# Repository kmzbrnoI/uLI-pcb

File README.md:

uLI – Ultimate LI PCB
=====================

uLI is a XpressNET &#8596; USB converter behaving as COM port in PC (CDC).

## uLI v5

* Designed in: KiCad 7
* Main Processor: PIC18F14K50
* Several enhancements from uLI v4, backward-compatible.
  - See releases/tags for a list of modifications from uLI v4.
* Firmware is same for v4 & v5.
* Authors: Jan Horacek (c) 2024

## uLI v4

* Deprecated.
* Designed in: Eagle 9
* Main Processor: PIC18F14K50
* Authors: Jan Horacek, Michal Petrilak (c) 2016

## Firmware

* [uLI-fw](https://github.com/kmzbrnoI/uLI-fw)
* [uLI-master-fw](https://github.com/kmzbrnoI/uLI-master-fw)

## Further reading

- [About XpressNET](http://www.opendcc.de/info/xpressnet/xpressnet_e.html)
- uLI meets [XpressNET specification v3](http://www.lenzusa.com/1newsite1/Manuals/xpressnet.pdf)
- uLI should also meet [XpressNET specification v3.6](http://wiki.rocrail.net/lib/exe/fetch.php?id=xpressnet-en&cache=cache&media=xpressnet:xpressnet-lan-usb-23151-v1.pdf) (available only in German)

## License

Content of the repository is provided under [Creative Commons
Attribution-ShareAlike 4.0
License](https://creativecommons.org/licenses/by-sa/4.0/) as openhardware
project. You may download any data, contribute to the project, create PCB
yourself or even sell it yourself.

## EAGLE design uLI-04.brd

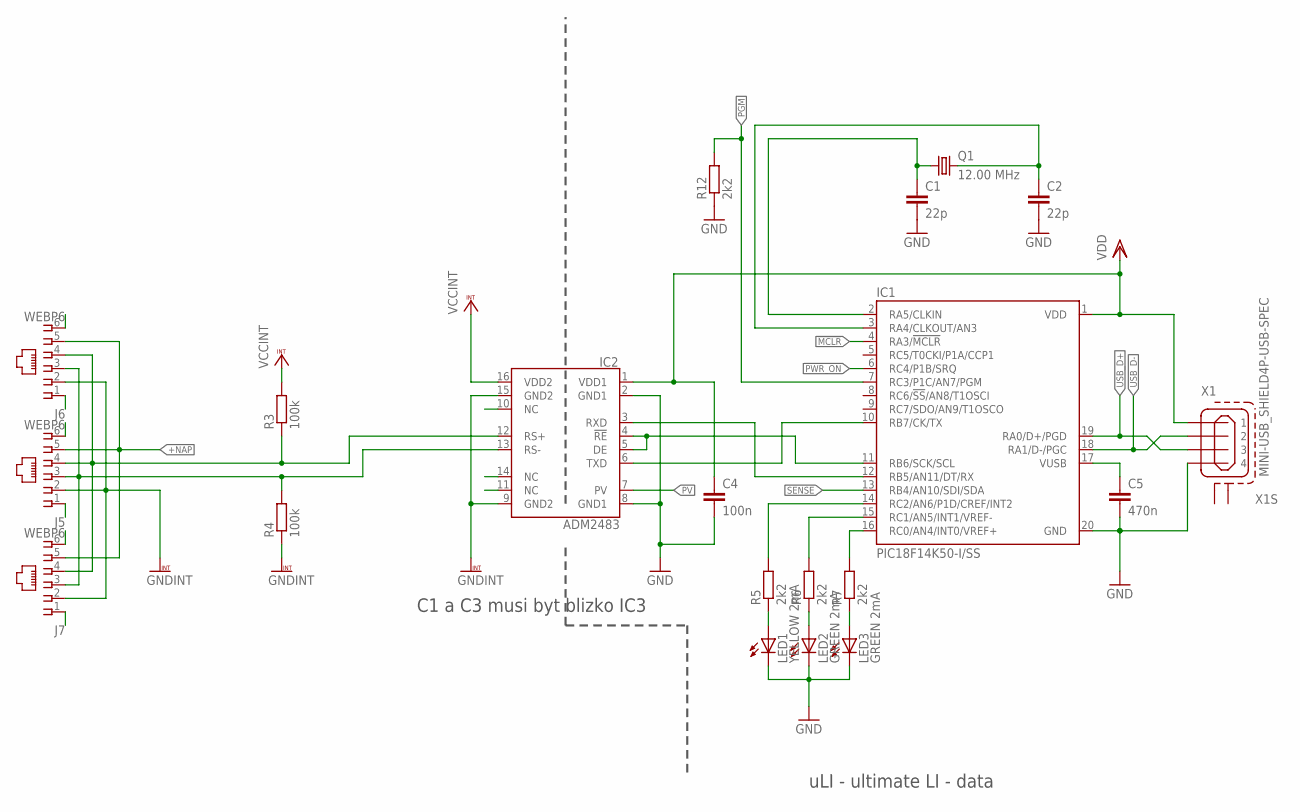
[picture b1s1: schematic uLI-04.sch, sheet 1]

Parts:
C1, C2: 22p; C0805
C4: 100n; C1206
C5: 470n; C1206
IC1: PIC18F14K50-I/SS; SSOP20
IC2: ADM2483; SO-16W
J5, J6, J7: WEBP6; WEBP6-6_SPEC2
LED1: YELLOW 2mA; LED3MM
LED2, LED3: GREEN 2mA; LED3MM
Q1: 12.00 MHz; HC49U70
R3, R4: 100k; R1206
R5, R6, R7, R12: 2k2; R1206
X1: MINI-USB_SHIELD4P-USB-SPEC; 85-32004-10X-SPEC

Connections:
!MCLR: IC1.4 (RA3/!MCLR!); also elsewhere on the board
+NAP: J5.5, J6.5, J7.5; also elsewhere on the board
BUS_A: IC2.12 (RS+), J5.4, J6.4, J7.4, R3.1
BUS_B: IC2.13 (RS-), J5.3, J6.3, J7.3, R4.2
GND: C1.2, C2.2, C4.2, C5.2, IC1.20 (GND), IC2.2 (GND1), IC2.8 (GND1), LED1.K (C), LED2.K (C), LED3.K (C), R12.1, X1.4; also elsewhere on the board
GNDINT: IC2.9 (GND2), IC2.15 (GND2), J5.2, J6.2, J7.2, R4.1; also elsewhere on the board
LED1: IC1.14 (RC2/AN6/P1D/CREF/INT2), R5.2
LED1_R: LED1.A, R5.1
LED2: IC1.15 (RC1/AN5/INT1/VREF-), R6.2
LED2_R: LED2.A, R6.1
LED3: IC1.16 (RC0/AN4/INT0/VREF+), R7.2
LED3_R: LED3.A, R7.1
unnamed: IC1.12 (RB5/AN11/DT/RX), IC2.3 (RXD)
NC2: IC2.14 (NC)
PGM: IC1.7 (RC3/P1C/AN7/PGM), R12.2; also elsewhere on the board
PROC_RX: IC1.10 (RB7/CK/TX), IC2.6 (TXD)
PROC_TE: IC1.11 (RB6/SCK/SCL), IC2.4 (!RE), IC2.5 (DE)
PV: IC2.7 (PV); also elsewhere on the board
PWR_ON: IC1.6 (RC4/P1B/SRQ); also elsewhere on the board
SENSE: IC1.13 (RB4/AN10/SDI/SDA); also elsewhere on the board
USB_D+: IC1.19 (RA0/D+/PGD), X1.3; also elsewhere on the board
USB_D-: IC1.18 (RA1/D-/PGC), X1.2; also elsewhere on the board
VBUS: C5.1, IC1.17 (VUSB)
VCCINT: IC2.16 (VDD2), R3.2; also elsewhere on the board
VDD: C4.1, IC1.1 (VDD), IC2.1 (VDD1), X1.1; also elsewhere on the board
XTAL1: C1.1, IC1.2 (RA5/CLKIN), Q1.1
XTAL2: C2.1, IC1.3 (RA4/CLKOUT/AN3), Q1.2

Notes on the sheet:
uLI - ultimate LI - data
C1 a C3 musi byt blizko IC3

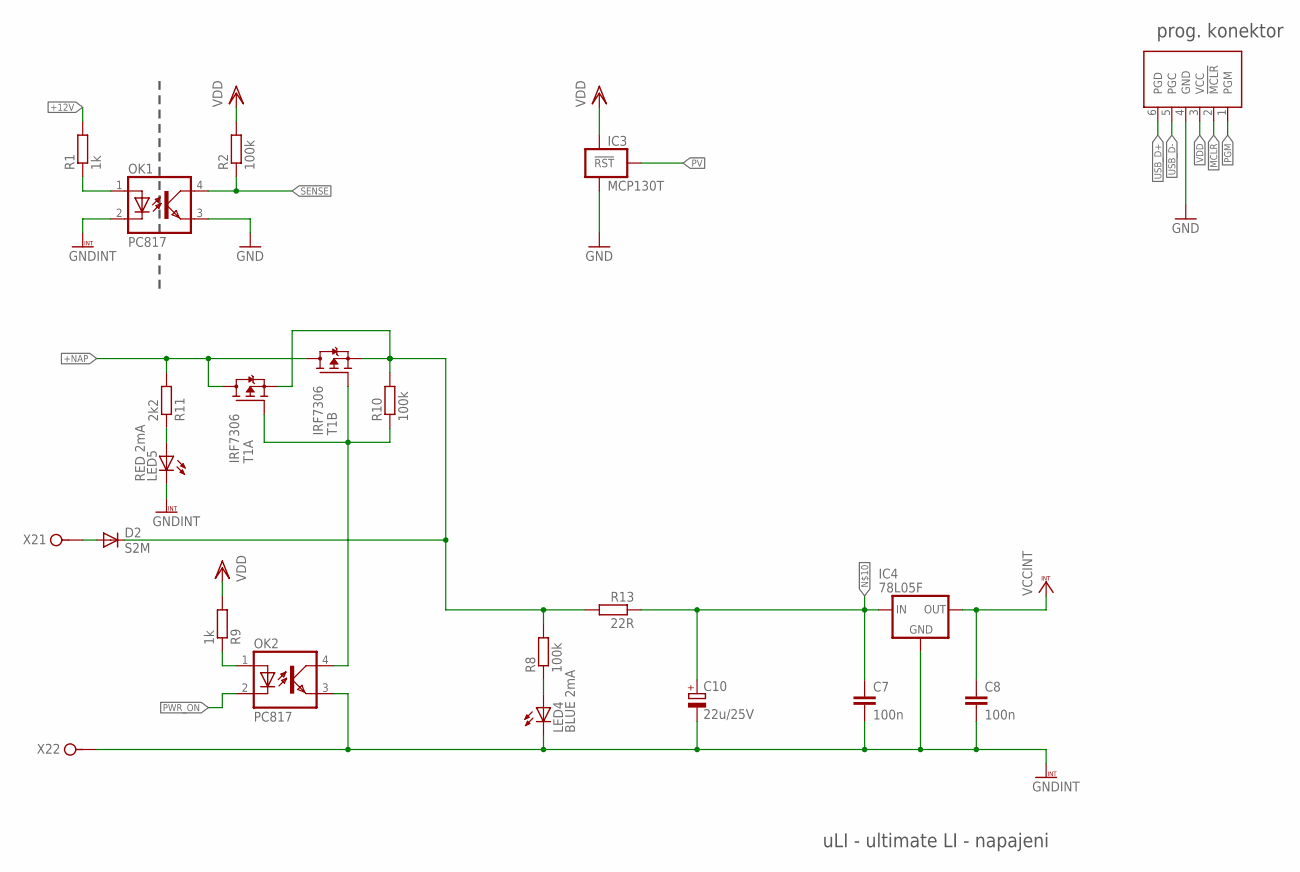
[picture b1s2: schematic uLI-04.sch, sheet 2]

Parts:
C7, C8: 100n; C1206
C10: 22u/25V; E2-5
D2: S2M; SMB
IC3: MCP130T; SOT23
IC4: 78L05F; SOT89
J1: PICPROG2-V; 6410-06-PICPROG
LED4: BLUE 2mA; LED3MM
LED5: RED 2mA; LED3MM
OK1, OK2: PC817; DIL04
R1, R9: 1k; R1206
R2, R8, R10: 100k; R1206
R11: 2k2; R1206
R13: 22R; R1206
T1: IRF7306; SO08-IRF
X2: ARK1550/2_S; ARK1550/2_SPEC

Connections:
!MCLR: J1.2 (!MCLR); also elsewhere on the board
+12V: D2.C, R1.2, R8.2, R10.2, R13.2, T1.1 (S), T1.3 (S)
+NAP: R11.2, T1.5 (D), T1.6 (D), T1.7 (D), T1.8 (D); also elsewhere on the board
+NAP2: D2.A, X2.1
BUS_SENSE: OK1.1 (A), R1.1
GND: IC3.3 (GND), J1.4 (GND), OK1.3 (EMIT); also elsewhere on the board
GNDINT: C7.2, C8.2, C10.-, IC4.2 (GND), IC4.2@1 (GND), LED4.K (C), LED5.K (C), OK1.2 (C), OK2.3 (EMIT), X2.2; also elsewhere on the board
unnamed: LED4.A, R8.1
unnamed: LED5.A, R11.1
unnamed: OK2.4 (COL), R10.1, T1.2 (G), T1.4 (G)
unnamed: OK2.1 (A), R9.1
unnamed: C7.1, C10.+, IC4.3 (VI), R13.1
PGM: J1.1 (PGM); also elsewhere on the board
PV: IC3.1 (!RST); also elsewhere on the board
PWR_ON: OK2.2 (C); also elsewhere on the board
SENSE: OK1.4 (COL), R2.1; also elsewhere on the board
USB_D+: J1.6 (PGD); also elsewhere on the board
USB_D-: J1.5 (PGC); also elsewhere on the board
VCCINT: C8.1, IC4.1 (VO); also elsewhere on the board
VDD: IC3.2 (VCC), J1.3 (VCC), R2.2, R9.2; also elsewhere on the board

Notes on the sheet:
uLI - ultimate LI - napajeni
prog. konektor

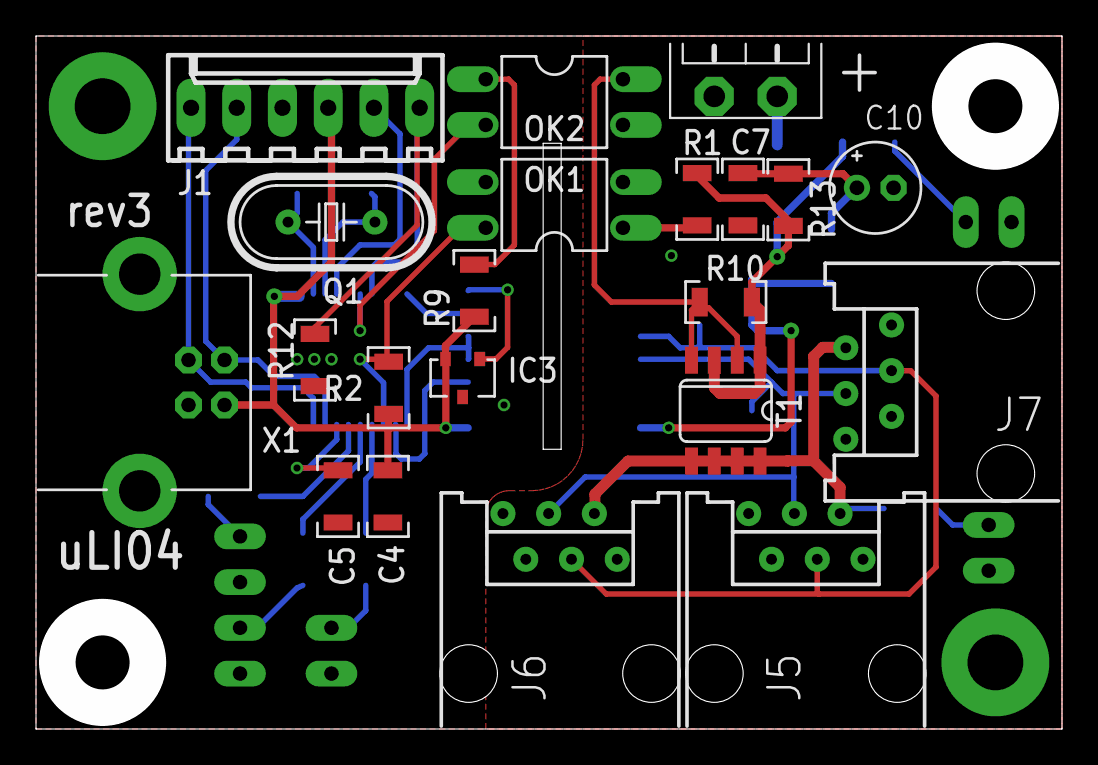
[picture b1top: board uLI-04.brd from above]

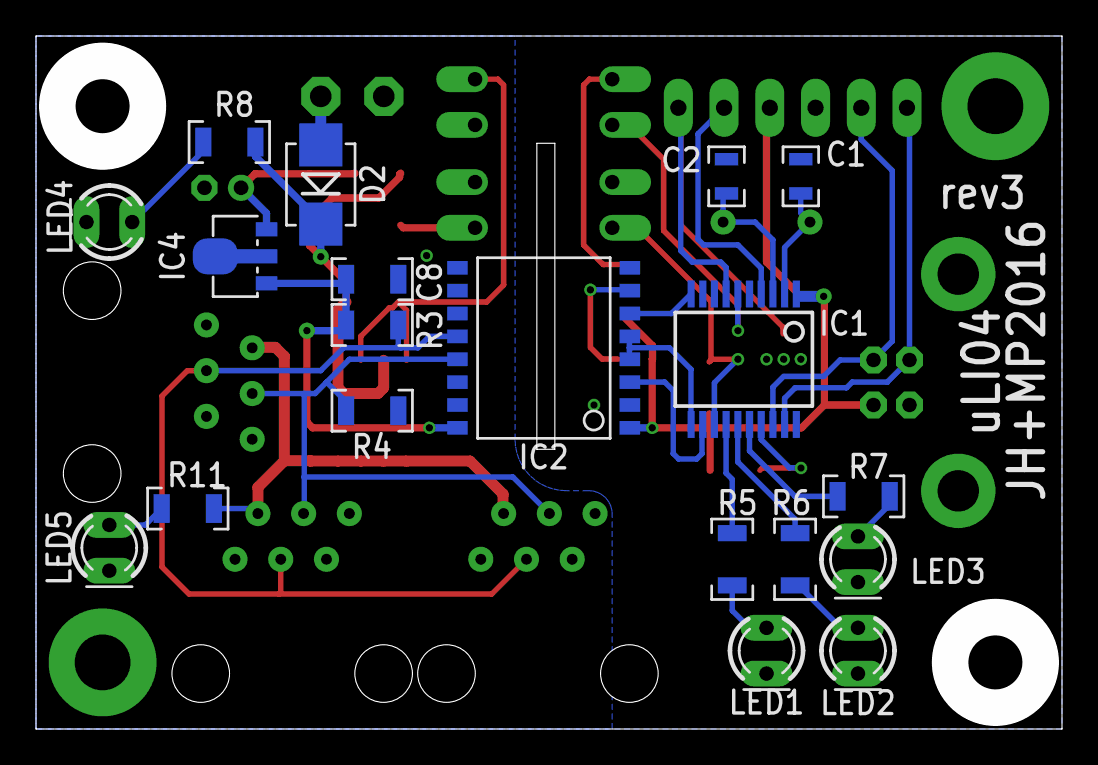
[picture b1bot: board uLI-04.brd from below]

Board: 2 copper layers, 57.0 x 38.5 mm, 40 parts (19 on the bottom side), 34 nets.

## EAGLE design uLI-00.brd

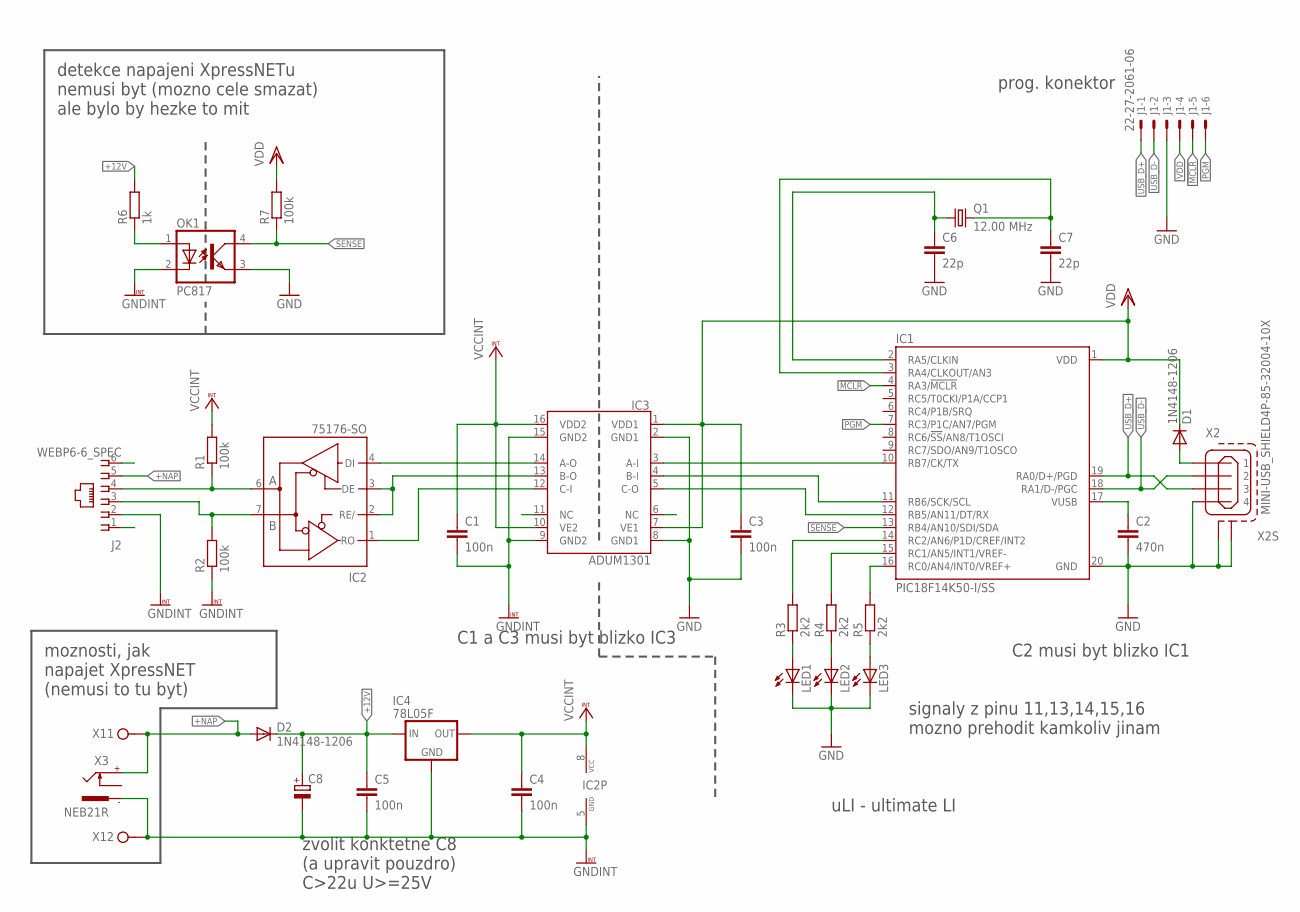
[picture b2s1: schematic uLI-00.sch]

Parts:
C1, C3, C4, C5: 100n; C1206
C2: 470n; C1206
C6, C7: 22p; C0805
C8: CPOL-EUE3.5-8L; E3,5-8L
D1, D2: 1N4148-1206; D1206
IC1: PIC18F14K50-I/SS; SSOP20
IC2: 75176-SO; SO08
IC3: ADUM1301; SO-16W
IC4: 78L05F; SOT89
J1: 22-27-2061-06; 6410-06
J2: WEBP6-6_SPEC
LED1, LED2, LED3: LED3MM
OK1: PC817; DIL04
Q1: 12.00 MHz; HC49U70
R1, R2, R7: 100k; R1206
R3, R4, R5: 2k2; R1206
R6: 1k; R1206
X1: ARK1550/2
X2: MINI-USB_SHIELD4P-85-32004-10X; 85-32004-10X
X3: NEB21R

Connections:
!MCLR: IC1.4 (RA3/!MCLR!), J1.5
+12V: C5.1, C8.+, D2.C, IC4.3 (VI), R6.2
+NAP: D2.A, J2.5, X1.1, X3.+
BUS_A: IC2.6 (A), J2.4, R1.1
BUS_B: IC2.7 (B), J2.3, R2.2
GND: C2.2, C3.2, C6.2, C7.2, IC1.20 (GND), IC3.2 (GND1), IC3.8 (GND1), J1.3, LED1.K (C), LED2.K (C), LED3.K (C), OK1.3 (EMIT), X2.4, X2.M1 (S1), X2.M2 (S2)
GNDINT: C1.2, C4.2, C5.2, C8.-, IC2.5 (GND), IC3.9 (GND2), IC3.15 (GND2), IC4.2 (GND), IC4.2@1 (GND), J2.2, OK1.2 (C), R2.1, X1.2, X3.-
unnamed: C2.1, IC1.17 (VUSB)
unnamed: LED1.A, R3.1
unnamed: LED2.A, R4.1
unnamed: IC1.12 (RB5/AN11/DT/RX), IC3.5 (C-O)
unnamed: IC1.10 (RB7/CK/TX), IC3.3 (A-I)
unnamed: IC1.11 (RB6/SCK/SCL), IC3.4 (B-I)
unnamed: IC2.4 (DI), IC3.14 (A-O)
unnamed: LED3.A, R5.1
unnamed: D1.A, X2.1
unnamed: IC1.14 (RC2/AN6/P1D/CREF/INT2), R3.2
unnamed: C7.1, IC1.3 (RA4/CLKOUT/AN3), Q1.2
unnamed: IC2.2 (RE/), IC2.3 (DE), IC3.13 (B-O)
unnamed: IC2.1 (RO), IC3.12 (C-I)
unnamed: C6.1, IC1.2 (RA5/CLKIN), Q1.1
unnamed: IC1.15 (RC1/AN5/INT1/VREF-), R4.2
unnamed: IC1.16 (RC0/AN4/INT0/VREF+), R5.2
unnamed: OK1.1 (A), R6.1
PGM: IC1.7 (RC3/P1C/AN7/PGM), J1.6
SENSE: IC1.13 (RB4/AN10/SDI/SDA), OK1.4 (COL), R7.1
USB_D+: IC1.19 (RA0/D+/PGD), J1.1, X2.3
USB_D-: IC1.18 (RA1/D-/PGC), J1.2, X2.2
VCCINT: C1.1, C4.1, IC2.8 (VCC), IC3.10 (VE2), IC3.16 (VDD2), IC4.1 (VO), R1.2
VDD: C3.1, D1.C, IC1.1 (VDD), IC3.1 (VDD1), IC3.7 (VE1), J1.4, R7.2

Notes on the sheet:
prog. konektor
uLI - ultimate LI
detekce napajeni XpressNETu nemusi byt (mozno cele smazat) ale bylo by hezke to mit
signaly z pinu 11,13,14,15,16 mozno prehodit kamkoliv jinam
moznosti, jak napajet XpressNET (nemusi to tu byt)
zvolit konktetne C8 (a upravit pouzdro) C>22u U>=25V
C1 a C3 musi byt blizko IC3
C2 musi byt blizko IC1

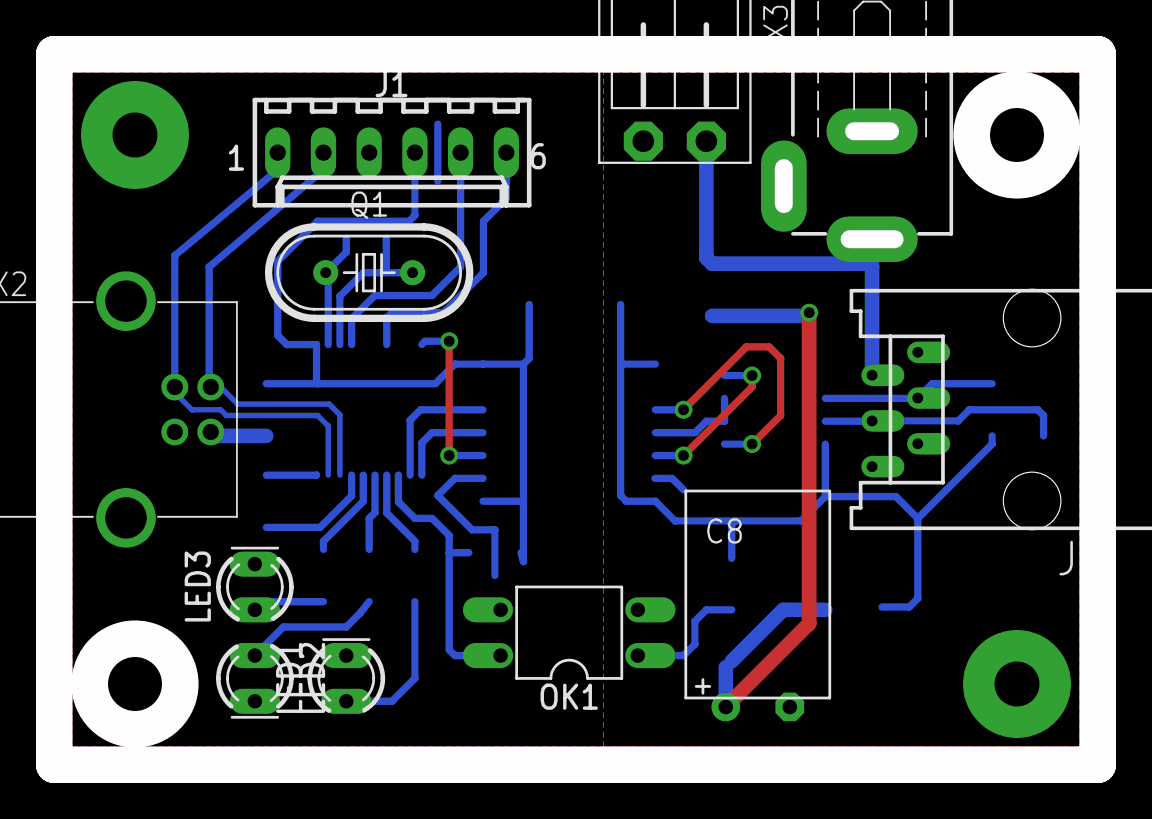
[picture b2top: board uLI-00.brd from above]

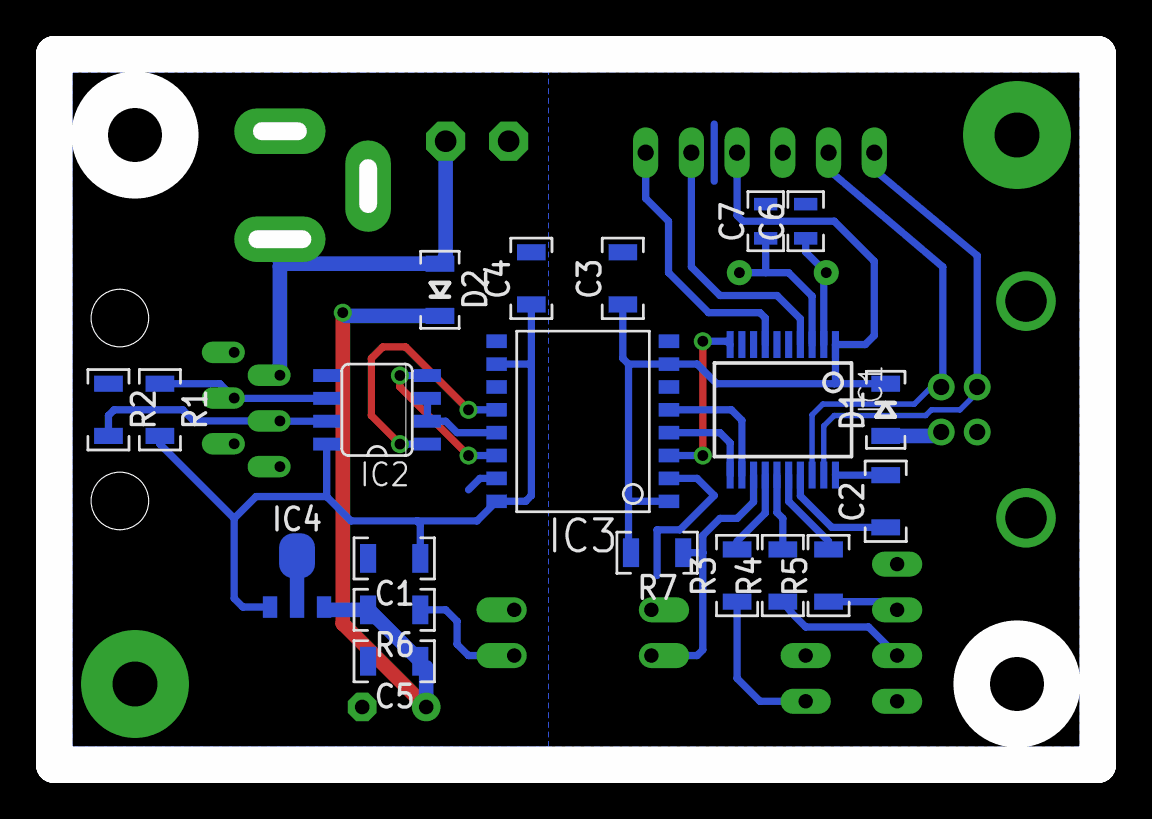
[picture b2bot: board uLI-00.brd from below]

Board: 2 copper layers, 58.0 x 39.5 mm, 31 parts (20 on the bottom side), 30 nets.

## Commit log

2016-05-23 Initial commit.
2016-05-23 Fix readme.
2016-06-12 Napajeci spoje ztlusteny na 0.4 mm.
2016-06-12 Pouzito DRU seedstudio.
2016-06-12 Odstranen prebytecny kondenzator 100 n.
2016-06-12 Presunuty popisky soucastek.
2016-06-12 Obrys krabicky presunut do vrstvy "krab".
2016-06-12 DRU -> electrow.
2016-08-14 Upraven osazovak.
2016-08-15 uLI-04 rev 2.
    Opraveny chyby uLI-04 zjistene behem testovani:
    * upraven obrys krabicky podle realnych rozmeru (zvetseno symtetricky 1 mm do sirky a 0.5 mm do vysky)
    * posunuty otvory pro srouby do krabicky o 0.5 mm v kazde ose smerrem ke kraji
    * prohozeno RX a TX mezi procesorem a ADUMem
    * opraveno zdcadlove zapojeni XpressNETich konektoru
2016-08-16 Odstranena ochrana dioda na vstupu z USB.
2016-08-17 Omezeni proudovych razu - schema
    Pridan na schema rezistor a zmensen kondenzator pred stabilizator.
    Editovano jen schema. Deska neupravena.
2016-08-17 Pridan brown-out reset pro PV pin
    Jen schema.
2016-08-21 Doplnena data pro frezovani krabicky.
2016-08-22 Dokreslen rezistor 22 Ohm.
2016-08-22 Dokreslen brown-down obvod do DPS.
2016-08-22 Upravena hodnota kondenzatoru XN na 22uF.
2016-08-22 Variantni zapojeni nabijeciho rezistoru.
2016-08-27 6-4 > 6-6, ploska J5.
    * Konektory WEBP 6-4 nahrazeny za WEBP 6-6. Close #3.
    * Pajeci ploska pobliz J5 odstranena. Close 2.
2016-08-27 Progrmaovaci konektor posunut o 0.5 mm doleva.
    Close #7.
2016-08-27 Odstranen kus dratu u stabilizatoru.
    Close #6.
2016-08-27 Posunut C5.
    Close $5.
2016-08-27 Velikost vnejsiho okraje prokovu -> 0.9 mm.
    Close #4.
2016-08-29 Drobne zmeny.
    * Upraveno DRC na bezpecnejsi mezery.
    * Prokovy nastaveny globalne na 0.4 mm.
    * Posunuta dioda S2M.
2016-08-29 Upraveny pozice hodnot a nazvu soucastek.
2016-08-29 Doplnen nepropojeny vodic.
2016-09-27 Doplnen rezistor 10k na pin PGM (#9).
2016-09-27 Rev3.
2016-09-27 Update README.
2017-10-16 Add colors of LEDs.
2017-10-16 Do not use optoislators in slave variant.
2017-10-16 Do blue LED in slave variant.
2017-10-27 Move texts in mounting scheme.
2017-10-29 Add note about CNC XY origin.
2018-08-01 Remove unused uLI boards.
2019-03-13 Add .NC files for box production.
2019-03-13 CNC: add notes to README.
2019-03-15 Change value of LED resistors based on reality.
2019-03-15 Update Eagle to v9.
2019-03-15 Set precise MCP's voltage.
2021-02-23 Minor board tweaks.
2024-02-15 Add uLI-05 KiCad empty project.
2024-02-15 Copy schematics from uLI-04.
    Changes compared to uLI-04:
    * Add SM712 protection to Ale asiXpressNET
    * Add ESDA6V1 protection to USB
    * Change prog connector pnout to match PICKit
    * Unify pull-ups to 10k
    * Connect ADM2483's PV directly to VCC
2024-02-15 Add another diode to power supply.
    So XpressNET devices do not drain our internal capacitors.
2024-02-15 Add mounting holes, use 1N5819 as schottky diodes.
2024-02-15 Add option to bridge IRF7306 (slave variant).
2024-02-15 Add DE pull-down.
2024-02-17 Use part names from uLI-04.
2024-02-17 Add footprints.
2024-02-17 Use USBLC6 for USB protection.
    Benefits:
    * USBLC6 is specifically designed for USB
    * It also protects VCC
2024-02-17 Add R16 distinguish resistor.
    To distinguish between uLI-4 & uLI-5 in firmware.
2024-02-18 pcb: import mechanical from uLI-4, draw outline.
2024-02-18 pcb: place connectors & LEDs.
    Place on same positions as in uLI-4.
2024-02-18 Add STL1550 power connector.
2024-02-18 pcb: wire USB part.
2024-02-19 pcb: wire XpressNET part.
2024-02-20 Add vias.
2024-02-20 Tweak silkscreen.
2024-02-20 Add LCSC numbers.
2024-02-20 Fix issues reported by DRC.
2024-02-22 Add fuses.
2024-02-24 Use SS34 as D2.
    SS34 supports larger maximum current.
2024-02-29 F1, F2, F3: add JLCPCB_IGNORE.
2024-02-29 Move uLI-04 data to 'uLI-04' directory.
2024-02-29 D1, D2: add JLCPCB_CORRECTION.
2024-02-29 Remove misplaced wire.
2024-02-29 Change 1N5819 LCSC.
2024-03-01 Add v5 to README.
2024-03-23 Use 3.0 drills for RJ12 connectors.
    So the RJ12 connectors fit into the holes more precisely.
2024-03-24 Fix C6 position.
    Was outside of the board, move to appropriate place.
